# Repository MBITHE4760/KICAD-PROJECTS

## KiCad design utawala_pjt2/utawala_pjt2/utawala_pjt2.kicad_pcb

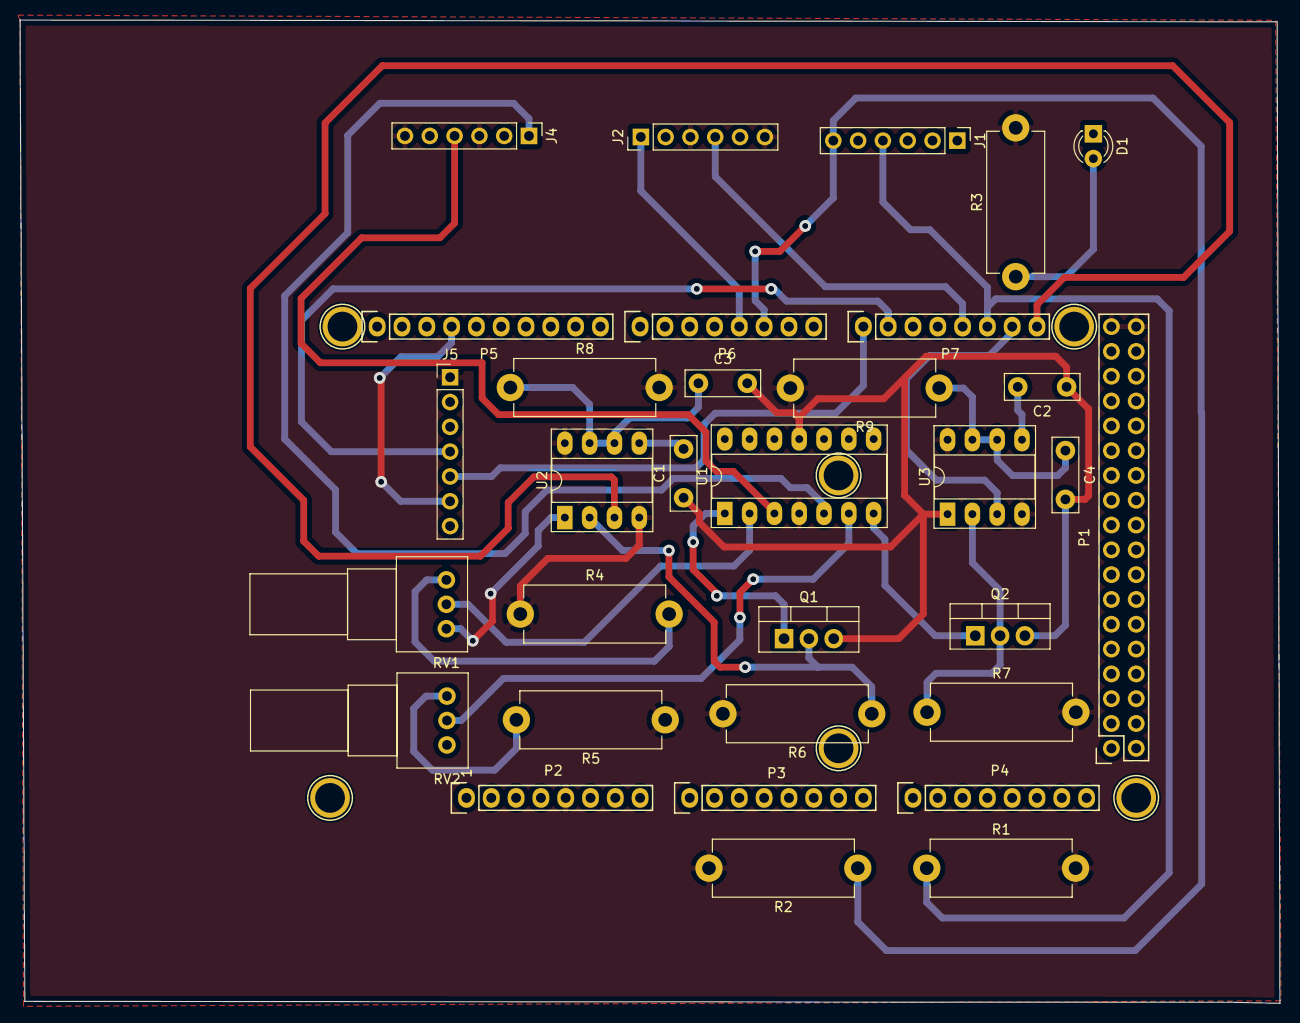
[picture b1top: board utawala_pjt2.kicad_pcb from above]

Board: 2 copper layers, 129.0 x 100.7 mm, 38 parts (0 on the bottom side), 25 nets.

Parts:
C1, C2, C3, C4: C; C_Disc_D7.5mm_W2.5mm_P5.00mm
D1: LED; LED_D3.0mm
J1, J2, J4: Conn_01x06_Female; PinHeader_1x06_P2.54mm_Vertical
J5: Conn_01x07_Female; PinHeader_1x07_P2.54mm_Vertical
P1: Digital; Socket_Strip_Arduino_2x18
P2: Power; Socket_Strip_Arduino_1x08
P3, P4: Analog; Socket_Strip_Arduino_1x08
P5: PWM; Socket_Strip_Arduino_1x10
P6: PWM; Socket_Strip_Arduino_1x08
P7: Communication; Socket_Strip_Arduino_1x08
P8, P9, P10, P11, P12, P13: CONN_01X01; Arduino_1pin
Q1, Q2: TIP122; TO-220-3_Vertical
R1, R2, R3, R4, R5, R6, R7, R8, R9: R; R_Axial_DIN0614_L14.3mm_D5.7mm_P15.24mm_Horizontal
RV1, RV2: R_POT; Potentiometer_Alps_RK097_Single_Horizontal
U1: LM324A; DIP-14_W7.62mm_Socket_LongPads
U2, U3: LM555xM; DIP-8_W7.62mm_Socket_LongPads

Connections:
CV_GENTS: RV1.2, U1.2
CV_LADIES: RV2.2, U1.6
GENTS_VOUT: Q1.2, R6.1, U2.2
GND: C1.1, C2.1, C3.2, C4.2, D1.1, J1.3, J1.5, J2.2, J2.5, J4.2, J4.5, J5.6, P1.1, P1.2, P2.6, P2.7, P5.4, Q1.3, Q2.3, RV1.3, RV2.3, U1.11, U2.1, U3.1
INT0_GENTS: P7.8, U2.3
INT1_LADIES: P7.7, U3.3
INT2_REED_GENTS: J1.4, P7.6, R1.1
INT3_FLOW_GENTS: J2.4, P7.5
INT4_REED_LADIES: J1.6, P6.6, R2.1
INT5_FLOW_LADIES: J2.1, P6.5
IR_GENTS: J4.4, U1.3
IR_LADIES: J4.1, U1.5
LADIES_VOUT: Q2.2, R7.1, U3.2
MCU_RX: J5.4, P7.2
MCU_TX: J5.5, P7.1
unnamed: C1.2, U2.5
unnamed: C2.2, U3.5
unnamed: C3.1, R8.1, U2.6, U2.7
unnamed: C4.1, R9.1, U3.6, U3.7
unnamed: D1.2, R3.1
unnamed: Q1.1, U1.1
unnamed: Q2.1, U1.7
unnamed: R4.2, RV1.1
unnamed: R5.2, RV2.1
VCC: J2.3, J2.6, J4.3, J4.6, J5.1, P1.35, P1.36, P2.5, R1.2, R2.2, R3.2, R4.1, R5.1, R6.2, R7.2, R8.2, R9.2, U1.4, U2.4, U2.8, U3.4, U3.8

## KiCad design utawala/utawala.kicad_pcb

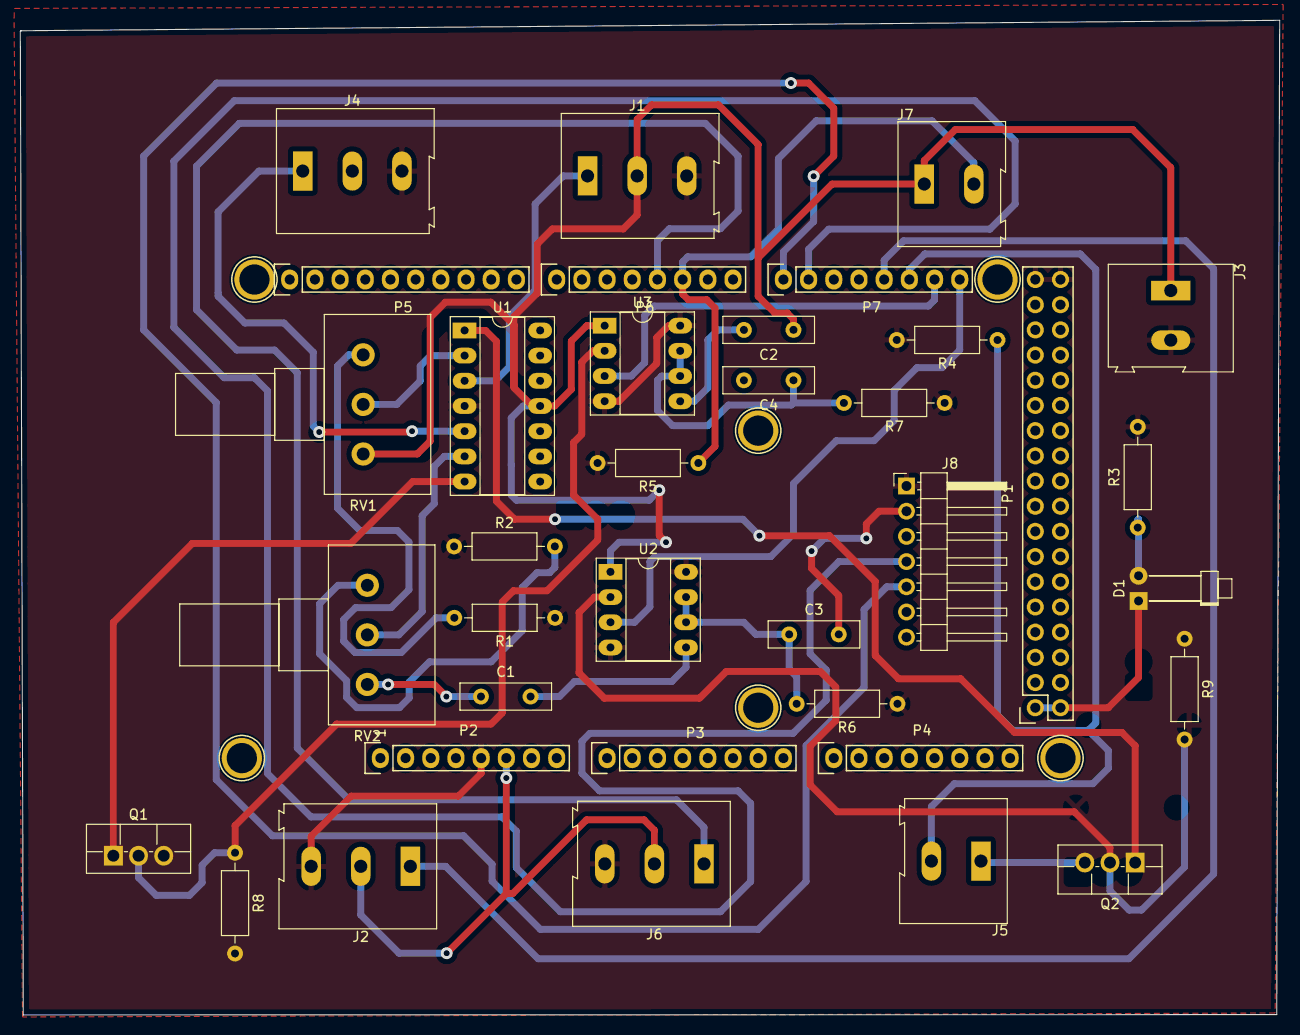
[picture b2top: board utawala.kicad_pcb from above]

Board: 2 copper layers, 127.0 x 100.3 mm, 42 parts (0 on the bottom side), 25 nets.

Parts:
C1, C2, C3, C4: C; C_Disc_D9.0mm_W2.5mm_P5.00mm
D1: LED; LED_D1.8mm_W1.8mm_H2.4mm_Horizontal_O6.35mm_Z8.2mm
J1, J2, J4, J6: Screw_Terminal_01x03; TerminalBlock_Altech_AK300-3_P5.00mm
J3, J5, J7: Screw_Terminal_01x02; TerminalBlock_Altech_AK300-2_P5.00mm
J8: Conn_01x07_Male; PinHeader_1x07_P2.54mm_Horizontal
P1: Digital; Socket_Strip_Arduino_2x18
P2: Power; Socket_Strip_Arduino_1x08
P3, P4: Analog; Socket_Strip_Arduino_1x08
P5: PWM; Socket_Strip_Arduino_1x10
P6: PWM; Socket_Strip_Arduino_1x08
P7: Communication; Socket_Strip_Arduino_1x08
P8, P9, P10, P11, P12, P13: CONN_01X01; Arduino_1pin
Q1, Q2: TIP122; TO-220F-3_Vertical
R1, R2, R3, R4, R5, R6, R7, R8, R9: R; R_Axial_DIN0207_L6.3mm_D2.5mm_P10.16mm_Horizontal
RV1, RV2: R_POT; Potentiometer_Alps_RK163_Single_Horizontal
U1: LM324A; DIP-14_W7.62mm_Socket_LongPads
U2, U3: NE555P; DIP-8_W7.62mm_Socket_LongPads

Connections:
CV_GENTS: RV1.2, U1.2
CV_LADIES: RV2.2, U1.6
GENTS_VOUT: Q2.2, R9.2, U2.2
GND: C1.1, C2.1, C3.2, C4.2, D1.1, J1.2, J2.2, J3.1, J4.2, J5.1, J6.2, J7.1, J8.2, P1.1, P1.2, P2.6, P2.7, P5.4, Q1.3, Q2.3, RV1.3, RV2.3, U1.11, U2.1, U3.1
INT0_GENTS: P7.8, U2.3
INT1_LADIES: P7.7, U3.3
INT2_REED_GENTS: J5.2, P7.6, R4.1
INT3_FLOW_GENTS: J2.1, P7.5
INT4_REED_LADIES: J7.2, P6.6, R5.1
INT5_FLOW_LADIES: J6.1, P6.5
IR_GENTS: J1.1, U1.3
IR_LADIES: J4.1, U1.5
LADIES_VOUT: Q1.2, R8.1, U3.2
MCU_RX: J8.4, P7.2
MCU_TX: J8.5, P7.1
unnamed: C1.2, U2.5
unnamed: C2.2, U3.5
unnamed: C3.1, R6.2, U2.6, U2.7
unnamed: C4.1, R7.2, U3.6, U3.7
unnamed: D1.2, R3.1
unnamed: Q1.1, U1.7
unnamed: Q2.1, U1.1
unnamed: R1.2, RV1.1
unnamed: R2.2, RV2.1
VCC: J1.3, J2.3, J3.2, J4.3, J6.3, J8.1, P1.35, P1.36, P2.5, R1.1, R2.1, R3.2, R4.2, R5.2, R6.1, R7.1, R8.2, R9.1, U1.4, U2.4, U2.8, U3.4, U3.8

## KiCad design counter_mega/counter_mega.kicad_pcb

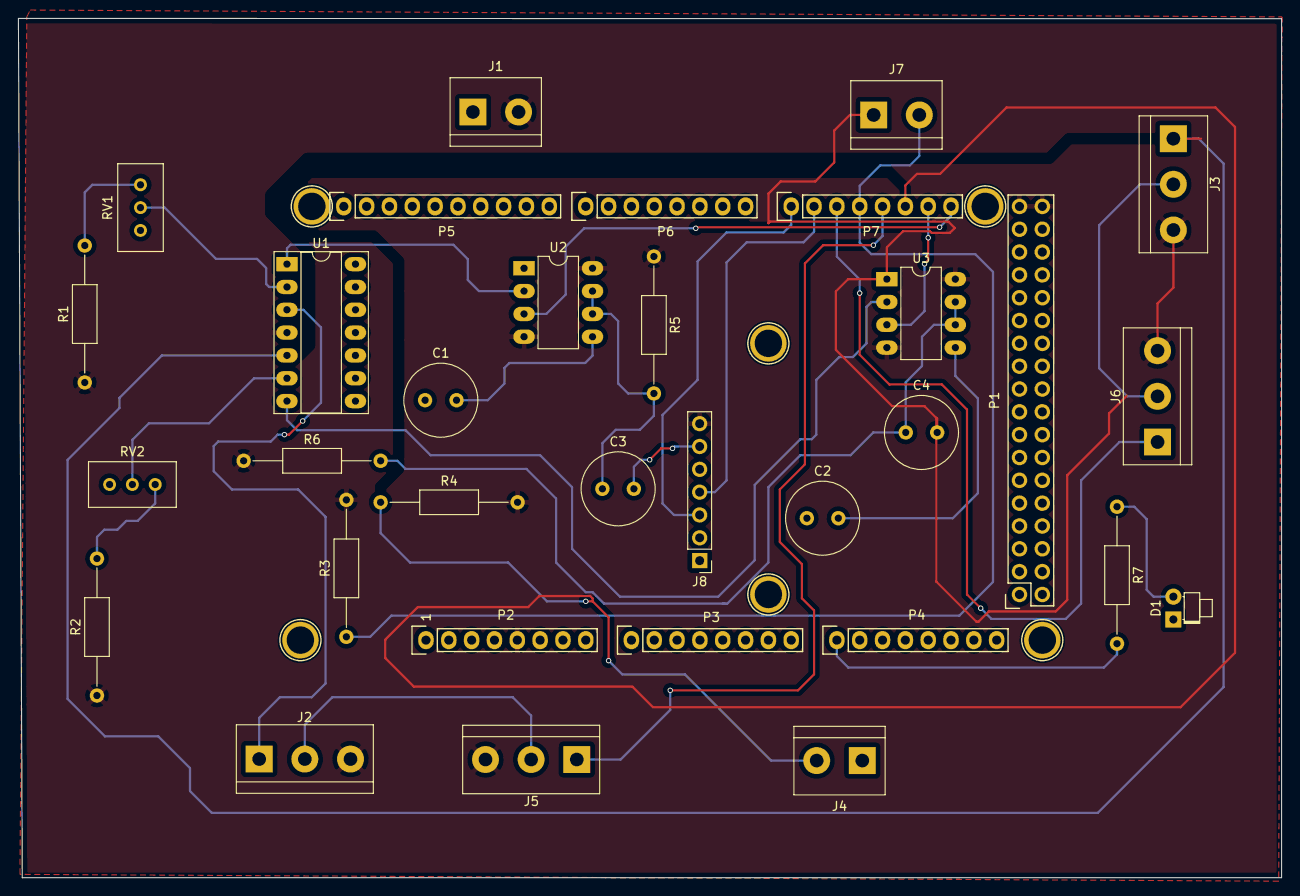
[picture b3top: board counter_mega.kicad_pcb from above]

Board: 2 copper layers, 140.6 x 95.6 mm, 38 parts (0 on the bottom side), 24 nets.

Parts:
C1, C2, C3, C4: C; C_Radial_D8.0mm_H11.5mm_P3.50mm
D1: LED; LED_D1.8mm_W1.8mm_H2.4mm_Horizontal_O1.27mm_Z1.6mm
J1, J4, J7: Screw_Terminal_01x02; TerminalBlock_bornier-2_P5.08mm
J2, J3, J5, J6: Screw_Terminal_01x03; TerminalBlock_bornier-3_P5.08mm
J8: Conn_01x07_Female; PinHeader_1x07_P2.54mm_Vertical
P1: Digital; Socket_Strip_Arduino_2x18
P2: Power; Socket_Strip_Arduino_1x08
P3, P4: Analog; Socket_Strip_Arduino_1x08
P5: PWM; Socket_Strip_Arduino_1x10
P6: PWM; Socket_Strip_Arduino_1x08
P7: Communication; Socket_Strip_Arduino_1x08
P8, P9, P10, P11, P12, P13: CONN_01X01; Arduino_1pin
R1, R2, R3, R4, R5, R6, R7: R; R_Axial_DIN0207_L6.3mm_D2.5mm_P15.24mm_Horizontal
RV1, RV2: R_POT; Potentiometer_Bourns_3296W_Vertical
U1: LM324A; DIP-14_W7.62mm_Socket_LongPads
U2, U3: LM555xM; DIP-8_W7.62mm_LongPads

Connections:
CV_GENTS: RV1.2, U1.2
CV_LADIES: RV2.2, U1.6
GENTS_VOUT: U1.1, U2.2
GND: C1.1, C2.1, C3.2, C4.2, D1.1, J1.1, J2.2, J3.2, J4.1, J5.2, J6.2, J7.1, J8.6, P1.1, P1.2, P2.6, P2.7, P5.4, RV1.3, RV2.3, U1.11, U2.1, U3.1
INT0_GENTS: P7.8, U2.3
INT1_LADIES: P7.7, U3.3
INT2_REED_GENTS: J4.2, P7.6, R4.1
INT3_FLOW_GENTS: J5.1, P7.5
INT4_REED_LADIES: J7.2, P7.4, R3.1
INT5_FLOW_LADIES: J6.1, P7.3
IR_GENTS: J2.1, U1.3
IR_LADIES: J3.1, U1.5
LADIES_VOUT: U1.7, U3.2
LED: P4.1, R7.2
MCU_RX: J8.4, P7.2
MCU_TX: J8.3, P7.1
unnamed: C1.2, U2.5
unnamed: C2.2, U3.5
unnamed: C3.1, R5.2, U2.6, U2.7
unnamed: C4.1, R6.2, U3.6, U3.7
unnamed: D1.2, R7.1
unnamed: R1.2, RV1.1
unnamed: R2.2, RV2.1
VCC: J1.2, J2.3, J3.3, J5.3, J6.3, J8.7, P1.35, P1.36, P2.5, R1.1, R2.1, R3.2, R4.2, R5.1, R6.1, U1.4, U2.4, U2.8, U3.4, U3.8

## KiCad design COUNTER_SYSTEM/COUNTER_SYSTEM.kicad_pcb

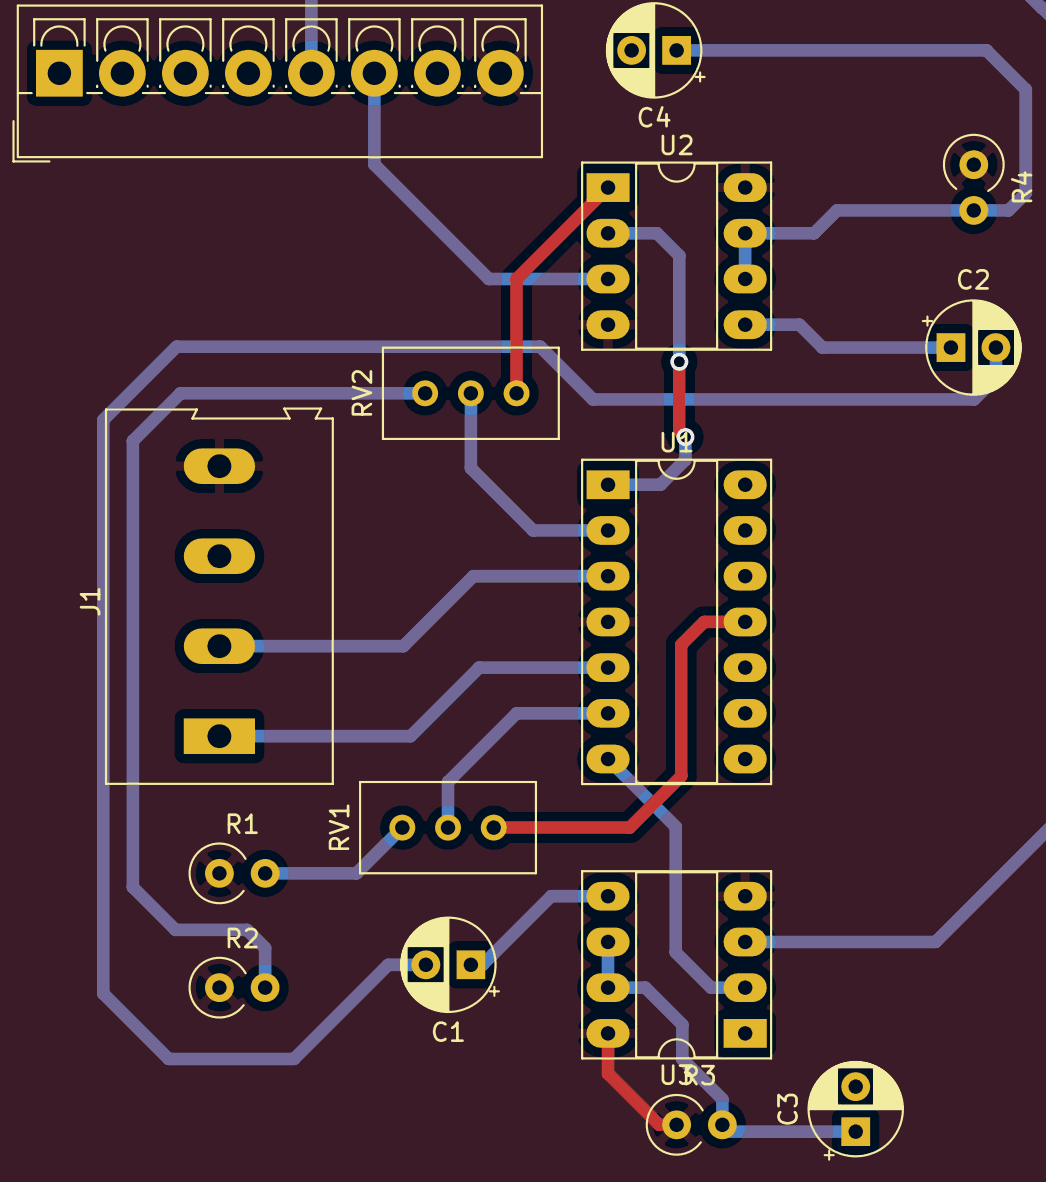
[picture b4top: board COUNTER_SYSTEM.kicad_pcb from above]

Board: 2 copper layers, 15 parts (0 on the bottom side), 17 nets.

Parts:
C1, C2, C3, C4: C; CP_Radial_D5.0mm_P2.50mm
J1: Screw_Terminal_01x04; TerminalBlock_Altech_AK300-4_P5.00mm
J2: Screw_Terminal_01x08; TerminalBlock_4Ucon_1x08_P3.50mm_Vertical
R1, R2, R3, R4: R; R_Axial_DIN0309_L9.0mm_D3.2mm_P2.54mm_Vertical
RV1, RV2: R_POT; Potentiometer_Bourns_3386C_Horizontal
U1: LM324A; DIP-14_W7.62mm_Socket_LongPads
U2, U3: NE555D; DIP-8_W7.62mm_Socket_LongPads

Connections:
CV_GENTS: RV2.2, U1.2
CV_LADIES: RV1.2, U1.6
Earth: C1.2, C2.2
GENTS_VOUT: U1.1, U2.2
GND: C3.2, C4.2, J1.3, J2.7, RV1.3, RV2.3, U1.11, U2.1, U3.1
INT0: J2.6, U2.3
INT1: J2.5, U3.3
IR_GENTS: J1.2, U1.3
IR_LADIES: J1.1, U1.5
LADIES_VOUT: U1.7, U3.2
unnamed: C1.1, U3.5
unnamed: C2.1, U2.5
unnamed: C3.1, R3.2, U3.6, U3.7
unnamed: C4.1, R4.2, U2.6, U2.7
unnamed: R1.2, RV1.1
unnamed: R2.2, RV2.1
VCC: J1.4, J2.8, R1.1, R2.1, R3.1, R4.1, U1.4, U2.4, U2.8, U3.4, U3.8
